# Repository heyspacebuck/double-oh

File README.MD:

# Double-Oh Battery

## Hardware version 2.7, Firmware version 1.0

This is the spiritual successor to the [SMOL](https://github.com/heyspacebuck/SMOL), a tiny PCB that interrupts battery output to make fun patterns. By designing around a 10mm-by-44mm LiPo cell, I've been able to add Wi-Fi connectivity, a USB connection for charging and programming, and a dangerous (but intriguing!) overvoltage mode.

The star of the show is the ESP32-PICO-D4, a 7mm-by-7mm powerhouse. It handles the wireless networking and various GPIOs.

Hardware developed in KiCad 5.1; firmware built in the Arduino IDE. Licensed/Licenced with the [CERN OHL](https://www.ohwr.org/project/cernohl/wikis/home). Documentation covered by [Creative Commons Attribution (CC-BY) 4.0](https://creativecommons.org/licenses/by/4.0/).

## Assembly, setup, installation

Bill of materials is [here](bom.md). An interactive HTML BOM is [here](/hardware/bom/ibom.html). Assembly and initial setup is covered [here](setup.md).

## Schematic

[A pdf version is also available.](/img/schematic.pdf)

## To do:

* Add pictures to [setup/assembly instructions](setup.md)
* Improve the user interface
* Generate renders

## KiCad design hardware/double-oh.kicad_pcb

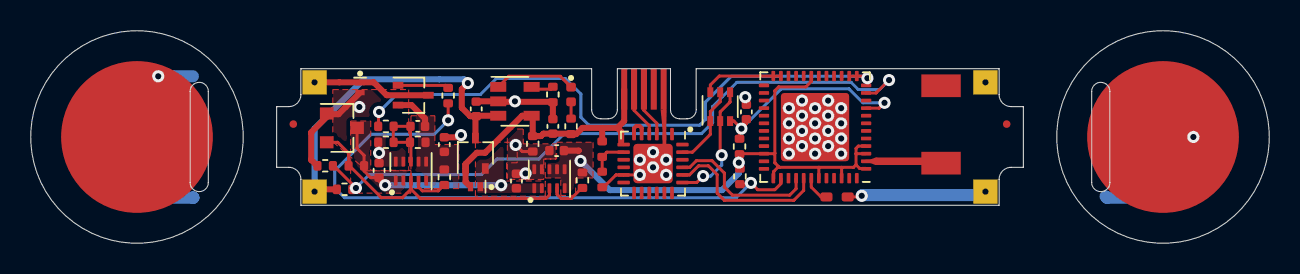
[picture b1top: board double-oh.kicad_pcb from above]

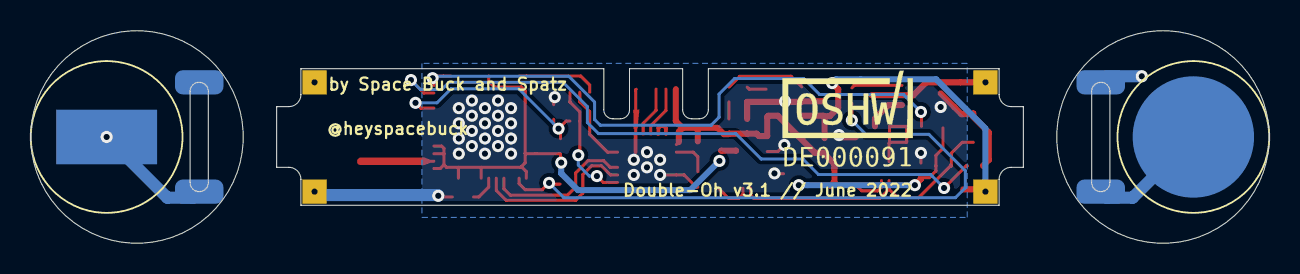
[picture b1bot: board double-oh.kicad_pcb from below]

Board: 2 copper layers, 81.6 x 14.0 mm, 51 parts (6 on the bottom side), 33 nets.

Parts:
AE1: NN01-102
C1, C2, C3, C4, C7: 4.7μF; C_0402_1005Metric
C5, C9: 10μF; C_0402_1005Metric
C6: 120pF; C_0402_1005Metric
D1: Blue LED; LED_0402_1005Metric
D2, D3: ‎PMEG6010AESBYL‎; SOD-993
J1: Unshielded USB Micro port; microusb_PCB_socket
J2, J3, J4, J12: Conn_01x01; main_board_solder_mount
J5, J6, J7, J13: Conn_01x01; cap_board_solder_mount
J8, J11: Conn_01x01; cap_contact
J9, J10: Conn_01x01; lipo_contact
JP1: Jumper_NO_Small; solder_bridge
Q1: MUN5213DW1; SOT-363_SC-70-6
Q2, Q3: SI1317DL-T1-BE3; SOT-323_SC-70
R1, R3, R5, R6, R7, R10, R11, R13, R16: 100kΩ; R_0402_1005Metric
R2: 3kΩ; R_0402_1005Metric
R4: 2kΩ; R_0402_1005Metric
R8: 1kΩ; R_0402_1005Metric
R9: 300kΩ; R_0402_1005Metric
R12: 330kΩ; R_0402_1005Metric
R14: 24kΩ; R_0402_1005Metric
R15: 47kΩ; R_0402_1005Metric
U1: ESP32-PICO-V3; QFN-48-1EP_7x7mm_P0.5mm_EP4.5x4.5mm
U2: CP2102N; QFN-24-1EP_4x4mm_P0.5mm_EP2.6x2.6mm
U3: TPSM828214SILR; microSiL-10
U4: TPSM82821SILR; microSiL-10
U5: MCP73831-2-OT; SOT-23-5
U6: BD48K34G; SOT-23

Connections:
0V: C1.1, C2.1, C3.2, C4.2, C5.1, C7.2, C9.1, D2.2, J1.5, J4.1, JP1.1, R2.1, R3.2, R5.1, R11.2, R15.1, U1.49, U2.2, U2.11, U2.25, U3.9, U3.10, U4.9, U4.10, U5.2, U6.1
3.3V: C5.2, R6.1, R7.1, R13.1, U1.1, U1.3, U1.4, U1.19, U1.34, U1.37, U1.43, U1.46, U3.5, U3.6, U3.7, U3.8
/D+: J1.3, U2.3
/D-: J1.2, U2.4
/Vbus: R14.2, R15.2, U2.8
ADC: R1.2, R3.1, U1.11
DAC: C6.2, R9.2, R11.1, R12.1, U4.8
DTR: Q1.1, Q1.5, U2.23
EN: C3.1, Q1.3, R13.2, U1.9
GPIO0: Q1.6, U1.23, U1.24
LIPO_ANODE: J6.1, J8.1, J9.1
LIPO_CATHODE: J5.1, J10.1
LIPO_V: C2.2, J3.1, Q3.3, R1.1, U5.3
unnamed: AE1.1, U1.2
unnamed: D1.1, U5.1
unnamed: D1.2, R4.2
unnamed: JP1.2, U1.42
unnamed: Q2.1, R8.2
unnamed: R2.2, U5.5
unnamed: R6.2, U3.4
unnamed: R7.2, R8.1, U1.38
unnamed: R10.2, U4.4
unnamed: R12.2, U1.12, U1.13, U1.14
unnamed: U2.5, U2.6
RTS: Q1.2, Q1.4, U2.19
RX_ESP: U1.40, U2.21
RX_USB: U1.41, U2.20
TOP_CAP: J7.1, J11.1
TPS_EN: R16.2, U3.3, U4.3, U6.2
TPS_VIN: C4.1, C7.1, D3.1, Q3.2, R16.1, U3.1, U3.2, U4.1, U4.2, U6.3
USB_VIN: C1.2, D3.2, J1.1, Q3.1, R4.1, R5.2, R14.1, U2.7, U5.4
batt_out: C6.1, C9.2, Q2.2, R9.1, R10.1, U4.5, U4.6, U4.7
to_top_cap: D2.1, J2.1, Q2.3

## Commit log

2020-01-04 Repo initialized without submodules
2020-01-04 Added submodule in the correct place this time
2020-01-04 Making progress on the settings page
2020-01-04 Network settings seem to be working!
2020-01-05 Update i2c net names
2020-01-05 Made a crude gif to show how the parts assemble
2020-01-07 Various small changes in anticipation of hardware
2020-01-07 Added software reset button
2020-01-07 Changed strings to char arrays, now EEPROM library works!
2020-01-07 Added a factory-reset pad to hardware
2020-01-07 Updated factory reset hardware to work with factory reset firmware
2020-01-07 Silly mistake; used wrong numbering for factory reset pins
2020-01-07 Fixed crystal layout and routing
2020-01-07 Update main board gerbers
2020-01-07 Update crystal caps
2020-01-07 Increased text size for legibility
2020-01-07 Cleaned up Factory-Reset code and also software-reset code
2020-01-09 Working on a version that, y'know, would actually work
2020-01-09 Updated silkscreen for legibility
2020-01-09 Added the component library (which should have been in here since the initial commit)
2020-01-09 Renamed footprints to use the correct library name
2020-01-10 Added pull-up and pull-down resistors that enable downloading new programs
2020-01-12 Updated gitignore
2020-01-12 Proof-of-concept that the ESP32 would fit on the proscribed space
2020-01-13 Cleaned up power-side routing and placement
2020-01-13 Fixed flyback diode orientation, will reposition power components later
2020-01-14 Added a filter cap to the EN line
2020-01-14 Cleaned up part layout
2020-01-15 Update to a more viable inductor package size
2020-01-15 Update diode to more viable package
2020-01-15 Minor touchups
2020-01-15 Laid out power components more cleanly
2020-01-16 Moved vias off of pads
2020-01-16 Thermal management
2020-01-16 More routing changes
2020-01-20 Added footprint for ALPS SSAJ switch, from collaborator Spatz
2020-01-21 Removed ESP_EEPROM from ESP32 firmware
2020-01-21 Updated (mostly) firmware for esp32
2020-01-21 Default settings set
2020-01-23 Up to v2.1 of design. No more digital potentiometer! Added credits for Spatz.
2020-01-23 Remove mentions of old repo name
2020-01-23 Update schematic to reflect correct DAC range
2020-01-24 Now powering CP2104 from USB instead of battery; added voltage monitoring
2020-01-24 Re-added model of antenna
2020-01-24 Removed rogue dot that remained on silkscreen from Digital Potentiometer
2020-01-24 Update readme and gerbers
2020-01-24 Actually updating readme this time
2020-01-24 Added MOSFET to switch between USB and battery power when plugged in
2020-01-24 Connected battery readout pin to an ADC
2020-01-24 Update gerbers
2020-01-24 Updated footprints and values to match what's available at Digikey.de
2020-01-27 Reverted to 0805 inductor size
2020-02-04 Small thermal relief added for buck converter
2020-02-05 Moved references off board
2020-02-10 Implemented SPIFFS
2020-02-11 Improved copper pour for ground plane (by Spatz)
2020-02-11 Added favicon
2020-02-13 Beginning to split into separate files
2020-02-14 Trying to figure out what's wrong with this code
2020-02-17 reordered HPPs
2020-02-17 Routing is working!
2020-02-17 I think I messed up a git filter/smudge somewhere...
2020-03-01 Trying a different buck converter IC
2020-03-01 Gerbers for TPS62400
2020-03-02 Working on TPS62400 routing
2020-03-02 routing tweaks
2020-03-15 Removed 3.3V connection to ESP32 pin 26
2020-03-16 Testing auto-BOM generation
2020-07-18 Getting back into it!
2020-07-20 minor changes
2020-07-20 Added a panelized version that can be made by most fab houses
2020-07-25 Updated readme, updated some comments in firmware
2020-07-25 Switched to Arduino
2020-07-25 Moved from platformio to arduino because it's less buggy
2020-07-26 guestbook backend seems to work
2020-07-26 Guestbook frontend done
2020-07-27 Added some info to index
2020-07-30 Updated factory-reset jumper to not use GPIO16, which is reserved
2020-07-30 Fixed stencil and 3d appearance of jumper
2020-08-01 Changed DAC resistors to be more 'normal' values
2020-08-01 Corrected the output pin code (now using sigma-delta) and added some experiments with voltage output
2020-08-01 Added battery management code
2020-08-01 Changed battery-voltage-reading circuit, upped hardware version number
2020-08-02 Updated panel gerber to v2.6
2020-08-02 Ignore zip files in gerber folder now
2020-08-06 Updated DAC resistor value
2020-08-06 Updated readme to reflect I'm using the Arduino IDE now
2020-08-07 Bigger pads for chip antenna
2020-08-07 Update panel and gerbers for larger antenna pads
2020-08-09 Rerouted for more thermal vias under buck converter
2020-08-16 Update DAC pin for battery level control
2020-08-16 Voltage control over web interface is working!
2020-08-16 increment firmware version
2020-08-24 Hardware update with additional safety feature
2020-08-31 Added interactive BOM
2020-08-31 Updated gerbers
2020-08-31 Added setup instructions
2020-09-03 Improve documentation
2020-09-03 Silly math error
2020-09-09 Implemented patterns for vibration output
2020-09-10 Preparing next live demo
2020-09-10 Finished twitter poll code I think
2020-09-11 Add quote-retweets to retweet count
2020-09-11 Fixed a cast error
2020-09-11 Corrected use of voltage supervisor
2020-09-11 Added pull-up resistor for open-drain supervisor
2020-09-11 Gerbers updated
2020-09-11 Update BOM, IBOM, and setup instructions
2020-09-11 Added some safety precautions for hardware v2.5
2020-09-11 Increased time for each retweet+like
2020-09-11 Final version going live
2020-09-14 Update firmware to use ledcwrite instead of sigmadeltawrite
2020-09-19 Typo fix
2020-09-24 Update file image and firmware
2020-09-24 Update firmware version to 1.0, very exciting
2020-09-28 Add open hardware logo, switch inductor to 0806 size
2020-09-30 Minor tweaks to inductor placement
2020-09-30 Added 'random' pattern
2020-09-30 Added 'single buzz' option
2020-10-04 Add pinball function
2020-10-07 Update default voltage for demo
2021-07-04 Switched to a new, smaller voltage supervisor
2021-07-05 Improve web interface a little
2021-07-06 Update panelized gerbers
2021-07-06 Added ridiculous Arduino Boards Manager hack
2021-07-07 Clean up schematic, instructions, and BOM
2021-07-07 Typo
2021-07-08 Trying a maybe dumb thing
2021-07-08 who needs recommended specs, am i right?
2021-07-08 Might need to bump this to 3.0 soon
2021-07-08 Using Harwin Shield Finger as spring contact on anode now
2021-07-08 Version 3 point oh!
2021-07-09 To be continued
2021-07-11 working on condensing the board
2021-07-12 bluh
2021-07-17 nearing 3.0 RC
2021-07-17 Updating documentation a bit
2021-07-18 I messed up; I didn't realize the U4WDH needs an external crystal. Switching to ESP32-PICO-V3 design.
2021-07-18 Forgot to finish routing
2021-07-18 Just for fun here's a version using the adorable MYRGP 3.3 regulator by Murata
2021-07-20 Small tweaks
2021-07-21 Put software battery check back in
2021-08-27 Update resistor values
2021-09-19 Tests are promising so far! Hopefully won't need a revision 3.1!
2021-09-20 Happy with firmware for now
2021-09-27 how long has that typo been there? embarrassing
2022-06-18 I don't even remember what changed
2022-06-18 Well dang, it looks like the ESP32 *can* be rotated after all
2022-12-27 Ignion antenna experiment

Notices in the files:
README.MD:
License: CC BY 4.0
